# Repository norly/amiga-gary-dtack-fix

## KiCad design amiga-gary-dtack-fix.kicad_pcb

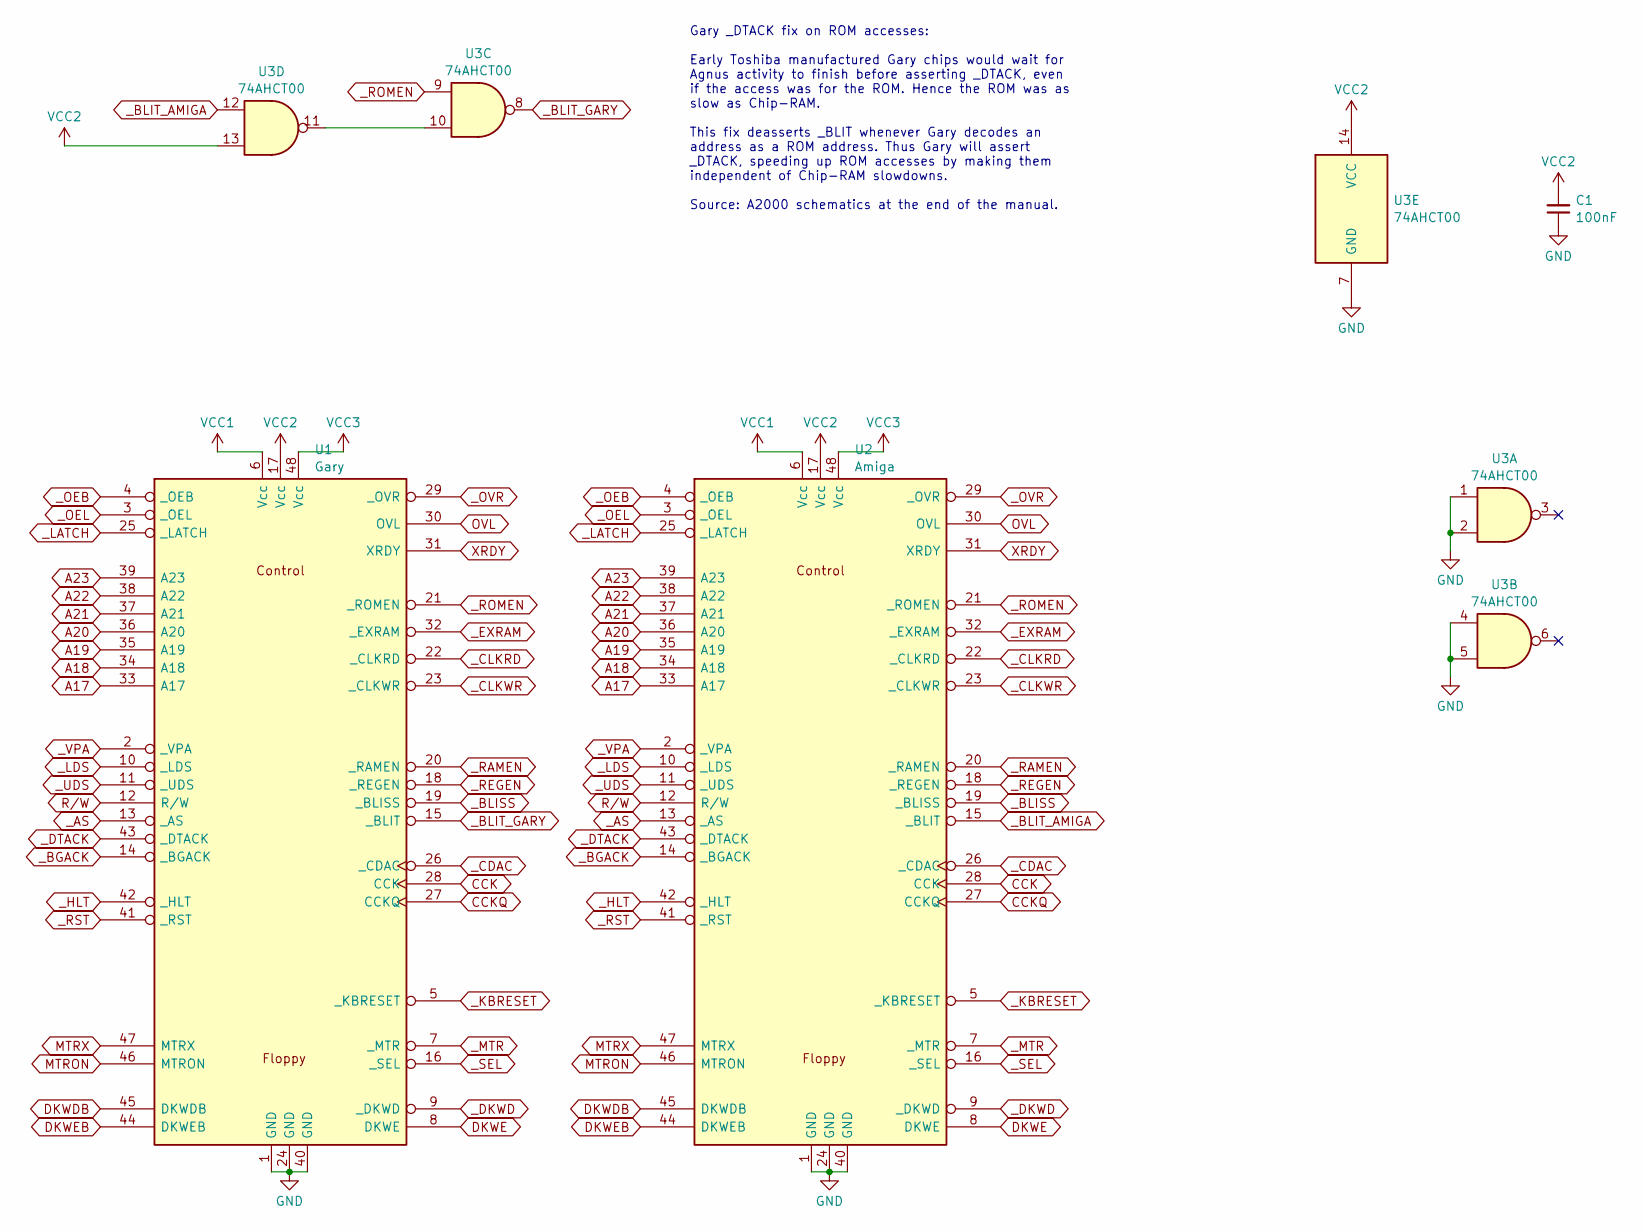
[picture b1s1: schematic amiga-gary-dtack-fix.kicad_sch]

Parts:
C1: 100nF; C_0805_2012Metric_Pad1.18x1.45mm_HandSolder; JLCPCB C49678
U1: Gary; DIP-48_W15.24mm_Socket_LongPads; LCSC C72120
U2: Amiga; DIP-48_W15.24mm_Socket_LongPads; LCSC C72120
U3: 74AHCT00; SOIC-14_3.9x8.7mm_P1.27mm; LCSC C155451

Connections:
A17: U1.33 (A17), U2.33 (A17)
A18: U1.34 (A18), U2.34 (A18)
A19: U1.35 (A19), U2.35 (A19)
A20: U1.36 (A20), U2.36 (A20)
A21: U1.37 (A21), U2.37 (A21)
A22: U1.38 (A22), U2.38 (A22)
A23: U1.39 (A23), U2.39 (A23)
CCK: U1.28 (CCK), U2.28 (CCK)
CCKQ: U1.27 (CCKQ), U2.27 (CCKQ)
DKWDB: U1.45 (DKWDB), U2.45 (DKWDB)
DKWE: U1.8 (DKWE), U2.8 (DKWE)
DKWEB: U1.44 (DKWEB), U2.44 (DKWEB)
GND: C1.1, U1.1 (GND), U1.24 (GND), U1.40 (GND), U2.1 (GND), U2.24 (GND), U2.40 (GND), U3.1, U3.2, U3.4, U3.5, U3.7 (GND)
MTRON: U1.46 (MTRON), U2.46 (MTRON)
MTRX: U1.47 (MTRX), U2.47 (MTRX)
unnamed: U3.10, U3.11
OVL: U1.30 (OVL), U2.30 (OVL)
R/W: U1.12 (R/W), U2.12 (R/W)
VCC1: U1.6 (Vcc), U2.6 (Vcc)
VCC2: C1.2, U1.17 (Vcc), U2.17 (Vcc), U3.13, U3.14 (VCC)
VCC3: U1.48 (Vcc), U2.48 (Vcc)
XRDY: U1.31 (XRDY), U2.31 (XRDY)
_AS: U1.13 (_AS), U2.13 (_AS)
_BGACK: U1.14 (_BGACK), U2.14 (_BGACK)
_BLISS: U1.19 (_BLISS), U2.19 (_BLISS)
_BLIT_AMIGA: U2.15 (_BLIT), U3.12
_BLIT_GARY: U1.15 (_BLIT), U3.8
_CDAC: U1.26 (_CDAC), U2.26 (_CDAC)
_CLKRD: U1.22 (_CLKRD), U2.22 (_CLKRD)
_CLKWR: U1.23 (_CLKWR), U2.23 (_CLKWR)
_DKWD: U1.9 (_DKWD), U2.9 (_DKWD)
_DTACK: U1.43 (_DTACK), U2.43 (_DTACK)
_EXRAM: U1.32 (_EXRAM), U2.32 (_EXRAM)
_HLT: U1.42 (_HLT), U2.42 (_HLT)
_KBRESET: U1.5 (_KBRESET), U2.5 (_KBRESET)
_LATCH: U1.25 (_LATCH), U2.25 (_LATCH)
_LDS: U1.10 (_LDS), U2.10 (_LDS)
_MTR: U1.7 (_MTR), U2.7 (_MTR)
_OEB: U1.4 (_OEB), U2.4 (_OEB)
_OEL: U1.3 (_OEL), U2.3 (_OEL)
_OVR: U1.29 (_OVR), U2.29 (_OVR)
_RAMEN: U1.20 (_RAMEN), U2.20 (_RAMEN)
_REGEN: U1.18 (_REGEN), U2.18 (_REGEN)
_ROMEN: U1.21 (_ROMEN), U2.21 (_ROMEN), U3.9
_RST: U1.41 (_RST), U2.41 (_RST)
_SEL: U1.16 (_SEL), U2.16 (_SEL)
_UDS: U1.11 (_UDS), U2.11 (_UDS)
_VPA: U1.2 (_VPA), U2.2 (_VPA)

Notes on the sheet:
Gary _DTACK fix on ROM accesses: Early Toshiba manufactured Gary chips would wait for Agnus activity to finish before asserting _DTACK, even if the access was for the ROM. Hence the ROM was as slow as Chip-RAM. This fix deasserts _BLIT whenever Gary decodes an address as a ROM address. Thus Gary wi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

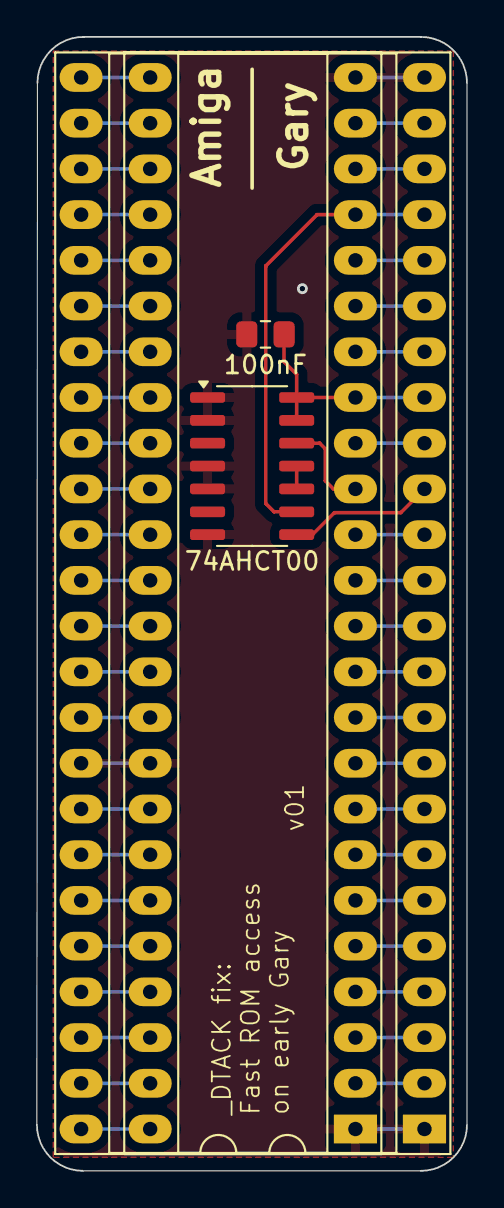
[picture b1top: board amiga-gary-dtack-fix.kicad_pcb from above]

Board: 2 copper layers, 23.9 x 63.0 mm, 4 parts (0 on the bottom side), 48 nets.

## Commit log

2024-07-26 Add .gitignore
2024-07-30 LICENSE: CC0
